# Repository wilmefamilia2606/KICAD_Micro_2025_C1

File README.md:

# KICAD_Micro_2025_C1
Board en Kicad del curso Microcontroladores C1 2025

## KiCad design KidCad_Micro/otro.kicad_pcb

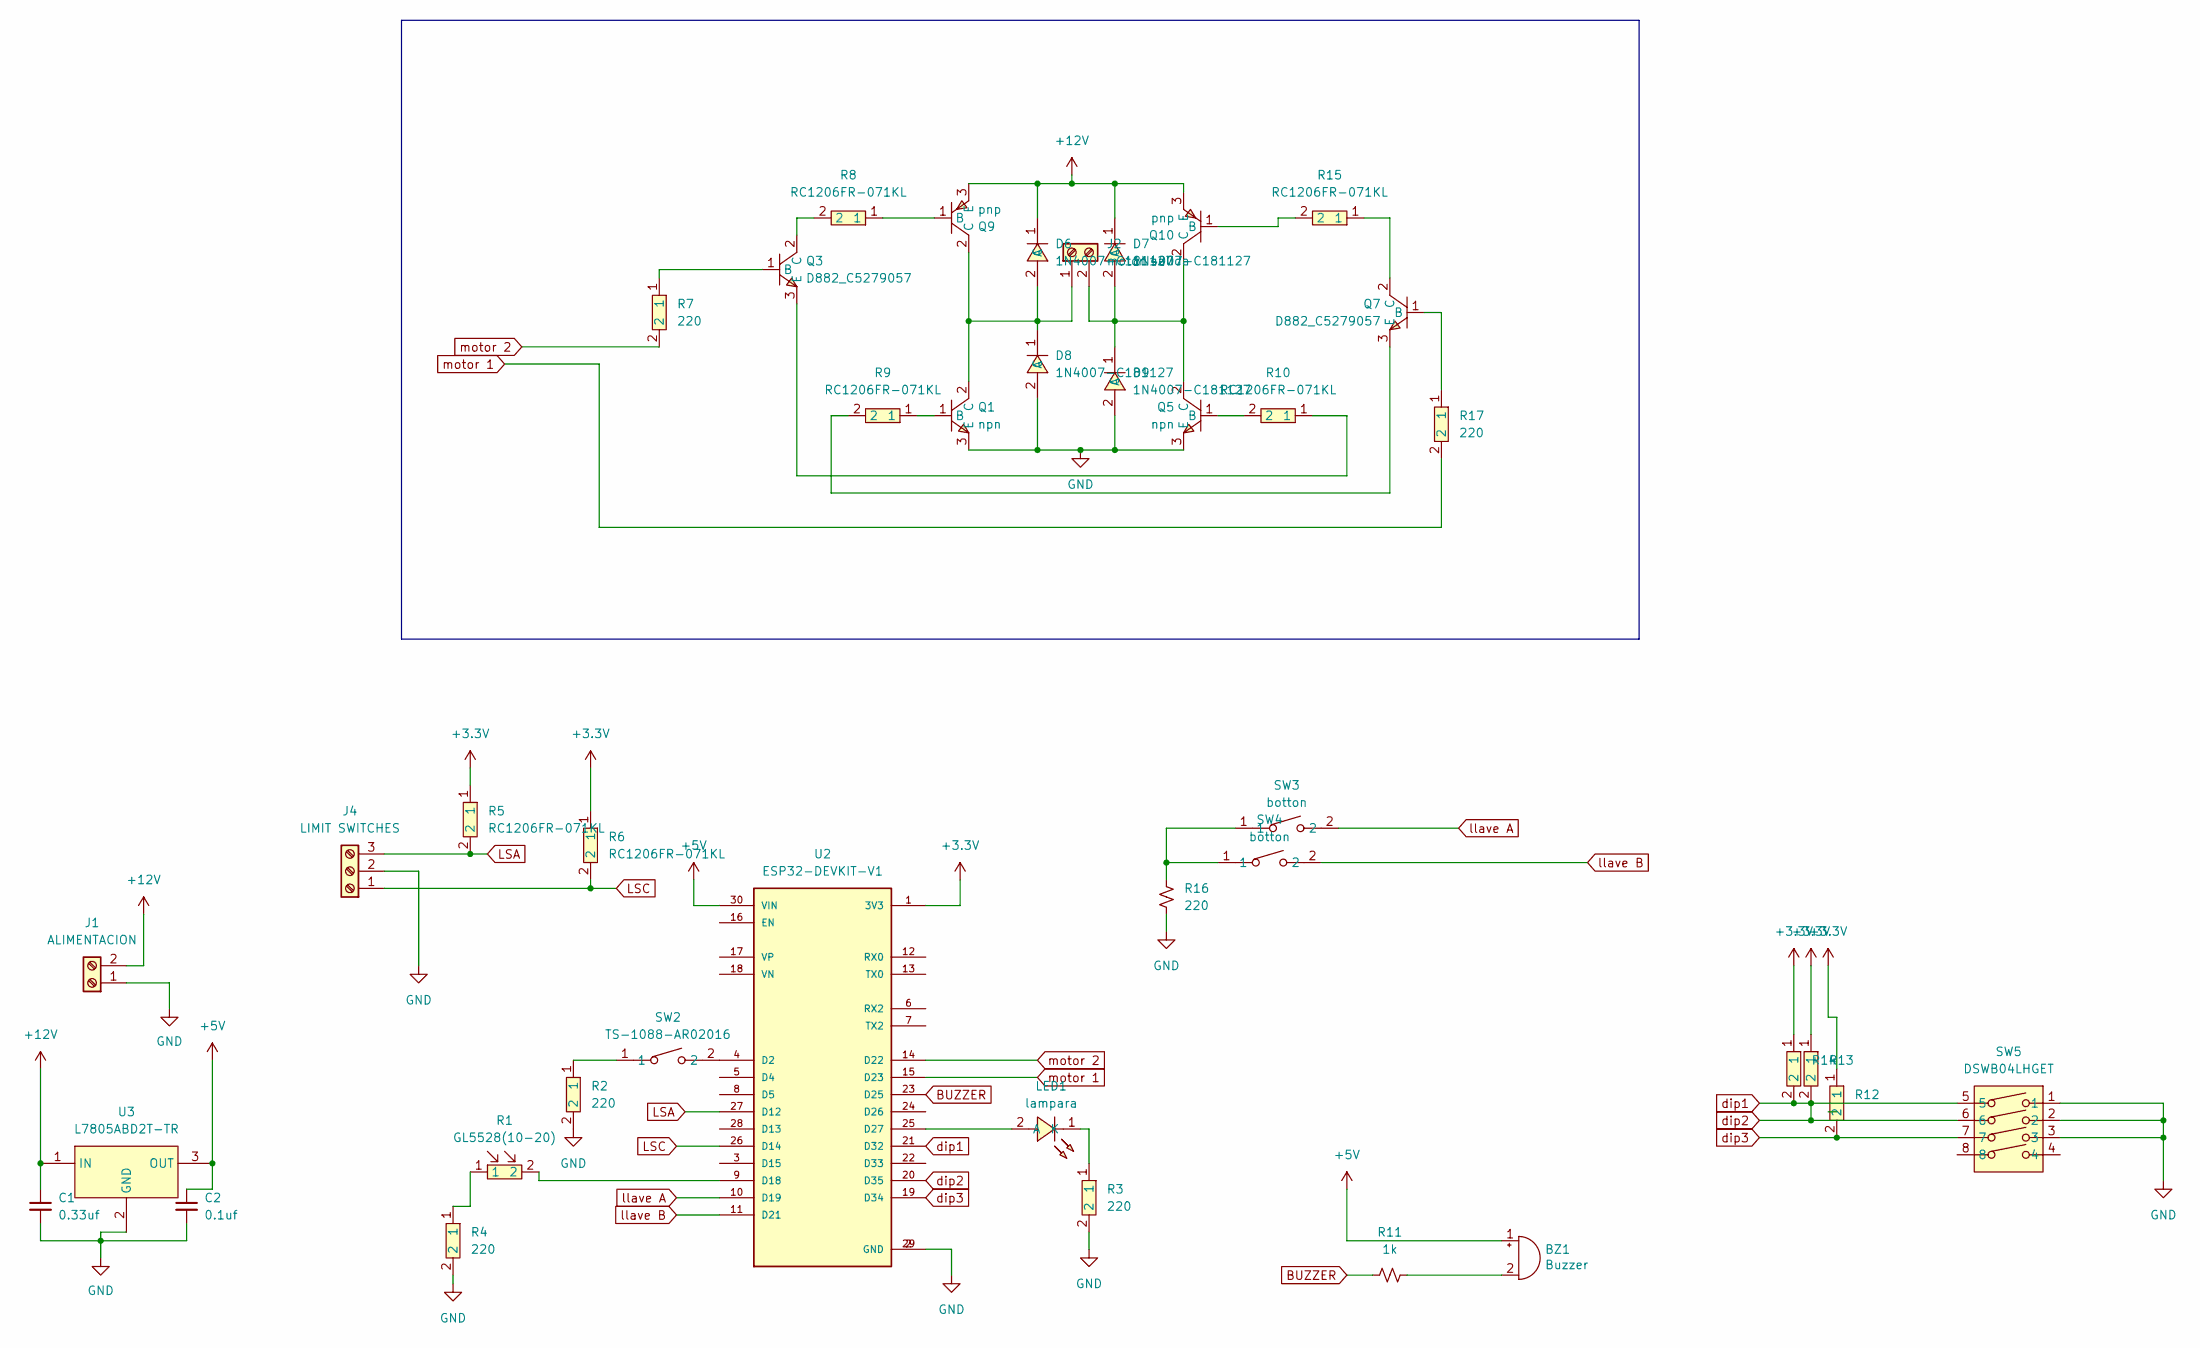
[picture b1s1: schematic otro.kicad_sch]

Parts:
BZ1: Buzzer; Buzzer_CUI_CPT-9019S-SMT
C1: 0.33uf; C_0402_1005Metric
C2: 0.1uf; C_0402_1005Metric
D6, D7, D8, D9: 1N4007-C181127; SOD-123F_L2.8-W1.8-LS3.7-RD; LCSC Part C181127
J1: ALIMENTACION; TerminalBlock_bornier-2_P5.08mm
J2: motor salida; TerminalBlock_bornier-2_P5.08mm
J4: LIMIT SWITCHES; TerminalBlock_bornier-3_P5.08mm; LCSC part C8404
LED1: lampara; LED0603-RD_RED; LCSC Part C965799
Q1, Q5: npn; SOT-89-3_L4.5-W2.5-P1.50-LS4.0-BR; LCSC Part C5279057
Q3, Q7: D882_C5279057; SOT-89-3_L4.5-W2.5-P1.50-LS4.0-BR; LCSC Part C5279057
Q9, Q10: pnp; SOT-89-3_L4.5-W2.5-P1.50-LS4.2-BR; LCSC Part C459827
R1: GL5528(10-20); RES-TH_L5.1-W4.3-P3.40-D0.5; LCSC Part C10081
R2, R3, R4, R7, R17: 220; R1206; LCSC Part C25363
R5, R6, R8, R9, R10, R12, R13, R14, R15: RC1206FR-071KL; R1206; LCSC Part C131398
R11: 1k; R_0402_1005Metric
R16: 220; R_0402_1005Metric
SW2: TS-1088-AR02016; SW-SMD_L3.9-W3.0-P4.45; LCSC Part C720477
SW3, SW4: botton; SW-SMD_L3.9-W3.0-P4.45; LCSC Part C720477
SW5: DSWB04LHGET; SW-TH_DSWB04LHGET; LCSC Part C99418
U2: ESP32-DEVKIT-V1; MODULE_ESP32_DEVKIT_V1; PARTREV N/A
U3: L7805ABD2T-TR; TO-263-2_L10.0-W9.2-P5.08-LS15.3-TL-CW; LCSC Part C86206

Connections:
+3.3V: R5.1, R6.1, R12.1, R13.1, R14.1, U2.1 (3V3)
+5V: BZ1.1 (+), C2.1, U2.30 (VIN), U3.3 (OUT)
+12V: C1.1, D6.1 (C), D7.1 (C), J1.2, Q9.3 (E), Q10.3 (E), U3.1 (IN)
BUZZER: R11.1, U2.23 (D25)
GND: C1.2, C2.2, D8.2 (A), D9.2 (A), J1.1, J4.2, Q1.3 (E), Q5.3 (E), R2.2, R3.2, R4.2, R16.2, SW5.1, SW5.2, SW5.3, U2.2 (GND), U2.29 (GND), U3.2 (GND)
LSA: J4.3, R5.2, U2.27 (D12)
LSC: J4.1, R6.2, U2.26 (D14)
unnamed: BZ1.2 (-), R11.2
unnamed: D6.2 (A), D8.1 (C), J2.1, Q1.2 (C), Q9.2 (C)
unnamed: D7.2 (A), D9.1 (C), J2.2, Q5.2 (C), Q10.2 (C)
unnamed: LED1.2 (A), U2.25 (D27)
unnamed: LED1.1 (K), R3.1
unnamed: Q1.1 (B), R9.1
unnamed: Q3.1 (B), R7.1
unnamed: Q3.2 (C), R8.2
unnamed: Q3.3 (E), R10.1
unnamed: Q5.1 (B), R10.2
unnamed: Q7.1 (B), R17.1
unnamed: Q7.2 (C), R15.1
unnamed: Q7.3 (E), R9.2
unnamed: Q9.1 (B), R8.1
unnamed: Q10.1 (B), R15.2
unnamed: R1.1, R4.1
unnamed: R2.1, SW2.1
unnamed: R16.1, SW3.1, SW4.1
unnamed: SW2.2, U2.4 (D2)
unnamed: R1.2, U2.9 (D18)
dip3: R12.2, SW5.7, U2.19 (D34)
llave A: SW3.2, U2.10 (D19)
llave B: SW4.2, U2.11 (D21)
motor 1: R17.2, U2.15 (D23)
motor 2: R7.2, U2.14 (D22)

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
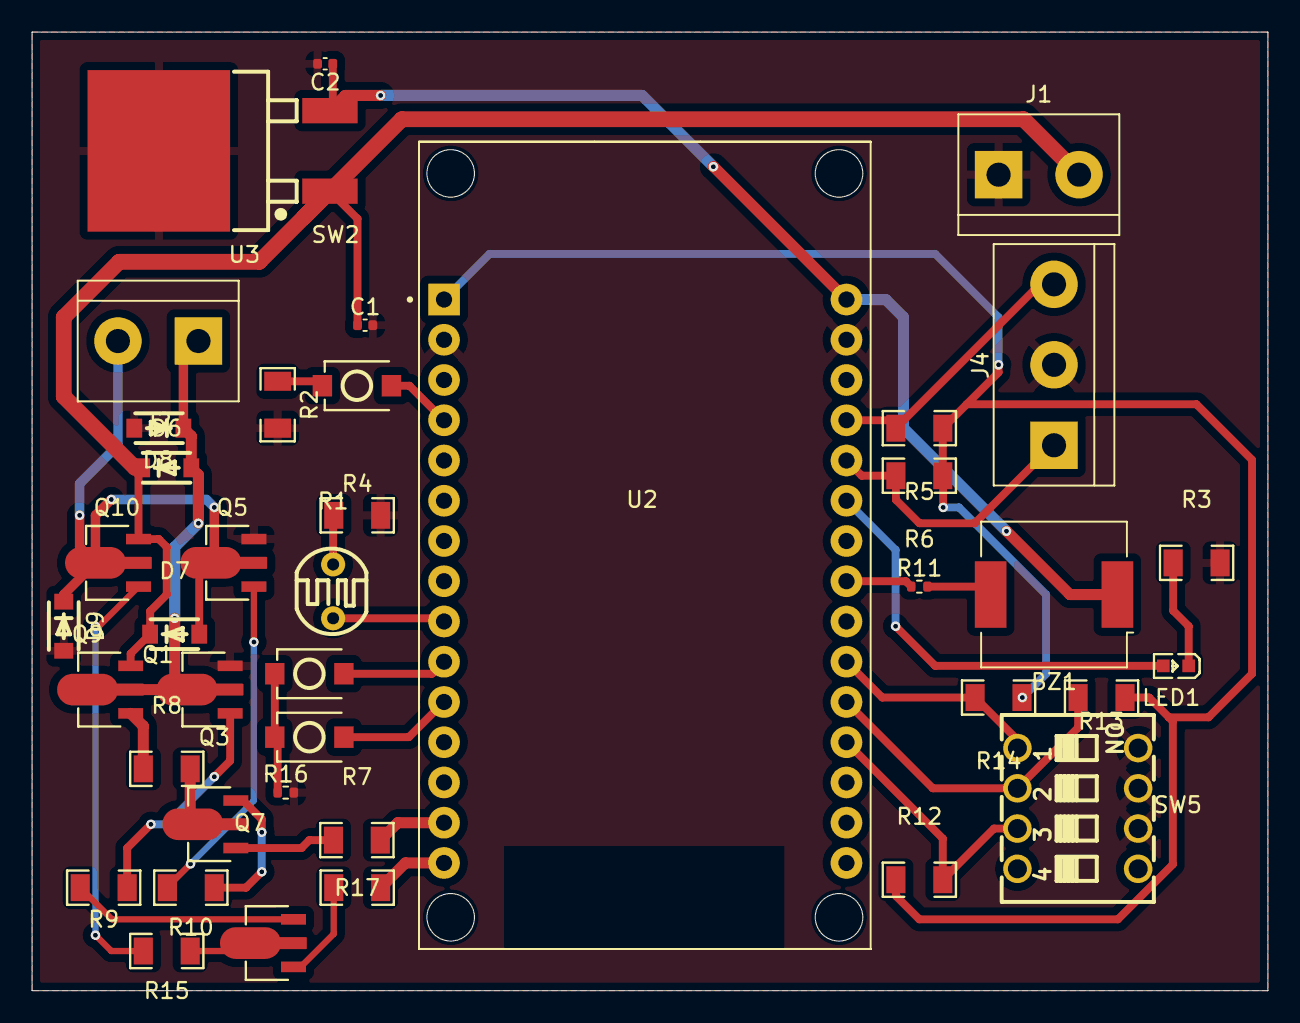
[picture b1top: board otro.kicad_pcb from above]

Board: 2 copper layers, 78.0 x 60.5 mm, 40 parts (0 on the bottom side), 34 nets.
